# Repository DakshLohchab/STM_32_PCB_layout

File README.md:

# STM_32_PCB_layout

## Overview
This repository contains the KiCad hardware design files for a custom printed circuit board (PCB) based on the STM32 microcontroller series[cite: 1]. The project includes the complete schematic, PCB layout, and 3D mechanical models necessary for fabrication, assembly, and enclosure integration[cite: 1].

## Features
*   **Microcontroller:** STM32 *(Replace with specific part number, e.g., STM32F401RCT6)*
*   **EDA Tool:** Designed entirely in KiCad (Version 6.0+)[cite: 1].
*   **Mechanical Integration:** Includes a pre-compiled `.stp` file for easy import into 3D modeling environments (SolidWorks, Fusion360, FreeCAD)[cite: 1].
*   *(Add any other specific board features here, like power delivery, interfaces, or form factor)*

---

## Repository Structure

The project files are located within the `STM_32_PCB_layout` directory[cite: 1]. Here is a breakdown of the core files:

*   **`STM_board_design.kicad_pro`**: The main KiCad project file[cite: 1]. Start here to open the project.
*   **`STM_board_design.kicad_sch`**: The schematic file containing the logical connections of the STM32 and peripheral components[cite: 1].
*   **`STM_board_design.kicad_pcb`**: The physical PCB layout and routing file[cite: 1].
*   **`STM_board_design.kicad_prl`**: Project-local settings, including layer visibility and specific UI preferences[cite: 1].
*   **`629105150521 (rev1).stp`**: A 3D STEP model representing the board or a specific mechanical component for CAD reference[cite: 1].
*   **`fp-info-cache`**: A cached file of footprint information to ensure the project loads quickly[cite: 1].
*   **`STM_board_design.kicad_sch-bak`**: An auto-generated backup of the schematic[cite: 1].

---

## Prerequisites

To view, edit, or generate manufacturing outputs for this project, you will need:
1.  **[KiCad EDA](https://www.kicad.org/):** Ensure you are running a version compatible with the `.kicad_pro` architecture.
2.  **3D Viewer (Optional):** A mechanical CAD tool to view the included `.stp` file.

---

## Getting Started

1.  **Clone the repository:**
```bash
    git clone [https://github.com/dakshlohchab/stm_32_pcb_layout.git](https://github.com/dakshlohchab/stm_32_pcb_layout.git)
    ```
2.  **Open the project:**
    Launch KiCad and select **File > Open Project...**
3.  **Navigate to the design:**
    Select the `STM_board_design.kicad_pro` file[cite: 1].
4.  **Explore:**
    Use the Schematic Editor to review the circuit, or the PCB Editor to view the board layout and run the Design Rule Checker (DRC).

---

## Manufacturing & Fabrication

To send this board to a manufacturer (e.g., JLCPCB, PCBWay, OSH Park):
1.  Open `STM_board_design.kicad_pcb`[cite: 1].
2.  Go to **File > Fabrication Outputs > Gerbers (.gbr)...**
3.  Generate the Gerber files according to your manufacturer's specific layer requirements.
4.  Generate the corresponding Drill files (`.drl`).
5.  *(Optional)* Export the BOM (Bill of Materials) and Pick & Place files if utilizing PCBA services.

---

## Contributing

Contributions, issues, and feature requests are welcome. Feel free to check the [issues page](../../issues) if you want to contribute.

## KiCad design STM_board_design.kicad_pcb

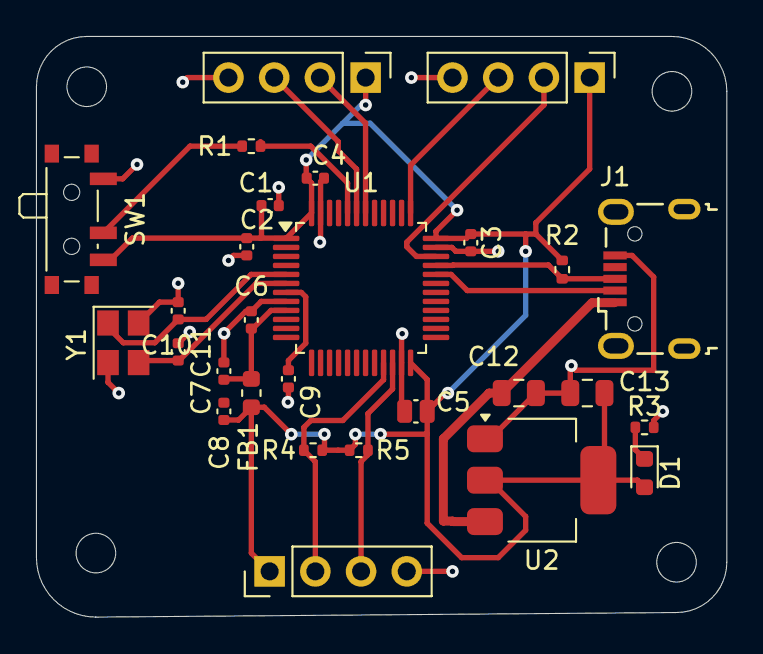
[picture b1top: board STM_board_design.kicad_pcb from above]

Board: 2 copper layers, 38.4 x 32.3 mm, 32 parts (0 on the bottom side), 18 nets.

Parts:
C1, C2, C3, C4, C9: 100n; C_0402_1005Metric
C5: 10u; C_0504_1310Metric_Pad0.83x1.28mm_HandSolder
C6: 10n; C_0402_1005Metric
C7, C8: 1u; C_0402_1005Metric
C10, C11: 10pf; C_0402_1005Metric
C12, C13: 22u; C_0805_2012Metric
D1: LED; LED_0603_1608Metric
FB1: 120R; L_0603_1608Metric
H1, H2, H3, H4: MountingHole; MountingHole_2.2mm_M2
J1: USB_B_Micro; USB_Micro-B_Wuerth_629105150521
J2, J3, J4: Conn_01x04_Pin; PinHeader_1x04_P2.54mm_Vertical
R1: 10k; R_0402_1005Metric
R2, R3, R4, R5: 1k5; R_0402_1005Metric
SW1: SW_SPDT; SW_SPDT_PCM12
U1: STM32F103C8T6; LQFP-48_7x7mm_P0.5mm
U2: AMS1117-3.3; SOT-223-3_TabPin2
Y1: 16 Mhz; Crystal_SMD_3225-4Pin_3.2x2.5mm

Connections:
+3.3V: C1.1, C2.1, C3.1, C4.1, C5.1, C8.1, C13.1, D1.2 (A), FB1.2, J2.1, J3.1, J4.1, R2.1, R4.1, R5.1, SW1.3 (C), U1.1 (VBAT), U1.24 (VDD), U1.36 (VDD), U1.48 (VDD), U2.2 (VO)
+3.3VA: C6.1, C7.1, FB1.1, U1.9 (VDDA)
/HSE_IN: C10.1, U1.5 (PD0), Y1.1
/HSE_OUT: C11.1, U1.6 (PD1), Y1.3
/I2C2_SCL: J4.2, R4.2, U1.21 (PB10)
/I2C2_SDA: J4.3, R5.2, U1.22 (PB11)
/NRST: C9.1, U1.7 (NRST)
/SWCLK: J2.3, U1.37 (PA14)
/SWDIO: J2.2, U1.34 (PA13)
/USART1_RX: J3.3, U1.43 (PB7)
/USART1_TX: J3.2, U1.42 (PB6)
/USB_D+: J1.x (D+), R2.2, U1.33 (PA12)
/USB_D-: J1.2 (D-), U1.32 (PA11)
GND: C1.2, C2.2, C3.2, C4.2, C5.2, C6.2, C7.2, C8.2, C9.2, C10.2, C11.2, C12.2, C13.2, J1.5 (GND), J2.4, J3.4, J4.4, R3.2, SW1.1 (A), U1.8 (VSSA), U1.23 (VSS), U1.35 (VSS), U1.47 (VSS), U2.1 (GND), Y1.2, Y1.4
unnamed: D1.1 (K), R3.1
unnamed: R1.2, SW1.2 (B)
unnamed: R1.1, U1.44 (BOOT0)
VBUS: C12.1, J1.1 (VBUS), U2.3 (VI)

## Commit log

2026-06-22 Revise README for STM32 PCB project details
    Updated the README to provide a comprehensive overview of the STM32 custom PCB layout project, including repository contents, prerequisites, getting started instructions, mechanical integration, and 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
2026-06-22 Add MIT License to the project
2026-06-22 Revise README for improved clarity and organization
    Updated README to enhance clarity and structure, including new sections on features, repository structure, prerequisites, getting started, manufacturing, and contributing.
2026-06-22 Delete license section from README
    Removed license section from README
